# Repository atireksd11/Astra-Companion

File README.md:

# Astra Companion- sigma boy 124

This repo holds the carrier PCB, the voice stack on the laptop, and notes for building Astra. Week 1 was the KiCad board. This week we are finishing the **audio module** on the printed body: a side speaker box, a neck that can pan, and a clean path for wires through the pivot. The plastic lives in [Astra-Companion-Cad](https://github.com/atireksd11/Astra-Companion-Cad). Mic and amp are still on the PCB (INMP441 and MAX98357A).

The board is built around a **ESP32-S3-DEVKITC-1** so the expensive module can stay on headers. If the first spin has a dumb mistake, I can swap the DevKit without rebuying everything.

**Where things stand:** schematic and layout are in the repo but the board is **not fab ready yet**. Power nets and the DevKit 3V3 tie still needed cleanup in the last pass. Do not order Gerbers until every net is routed and DRC is clean.

## The PCB

MPU-6050 for balance, DRV8833 for two N20 channels, TP4056 + MT3608 + AP2112K for battery and rails, dual GC9A01 round displays on SPI, INMP441 and MAX98357A for audio, plus fuel gauge, RTC, ToF, and microSD on the schematic. For what is actually on the board right now, use [hardware/BOM2.md](hardware/BOM2.md) (the older planning list drifted).

Open the project in KiCad 10: [hardware/astracompanion/](hardware/astracompanion/). Parts list for grants: [hardware/bom.csv](hardware/bom.csv). Notes on cost tiers: [hardware/BOM_SUMMARY.md](hardware/BOM_SUMMARY.md). When routing is done, plot Gerbers into [hardware/src/](hardware/src/).

## This week: audio module and neck

The CAD shows how the speaker panel bolts to the side of the torso, how the driver sits behind the grille, and how the head stack sits on bearings so it can turn without chewing up PETG.

**Parts we ordered ($27.94 before tax and shipping)**

| Part | Qty | Unit | Total | Where |
|------|-----|------|-------|-------|
| [PGN 608-ZZ ball bearings, 10 pack](https://www.amazon.ca/gp/product/B07XLV1W2M/ref=ox_sc_act_title_2?smid=A3RMJZMAP3U4RK&psc=1) (8 by 22 by 7 mm) | 10 | $1.30 | $12.95 | Amazon.ca |
| [MG90S metal gear micro servo, 2 pack](https://www.amazon.ca/gp/product/B0BHYHKF2P/ref=ox_sc_act_title_1?smid=A1AEYBYG92X8UY&psc=1) | 2 | $7.50 | $14.99 | Amazon.ca |
| Tax and shipping | | | about $5 | Prime / domestic |

Unit price is per piece. The totals are the pack prices Amazon charges. The bearing pack gives you spares after you use two on the neck. The MG90S pack gives you one pan servo and one spare (or a future tilt). Full writeup and grant CSV: [hardware/BOM_AUDIO_MODULE.md](hardware/BOM_AUDIO_MODULE.md) and [hardware/bom-audio-module.csv](hardware/bom-audio-module.csv).

Exploded view of the head, speaker side panel, and neck stack:

Rear view with the vented speaker box on the body:

Inside the torso showing the speaker and board bay:

Side panel, gasket plates, and speaker mount detail:

Voice on the laptop (wake word, STT, TTS) is documented under [docs/VOICE_SETUP.md](docs/VOICE_SETUP.md) and [server/README.md](server/README.md). The robot firmware streams audio to that bridge when you are ready to test on hardware.

## Firmware

Arduino on ESP32 already runs FreeRTOS, so the firmware splits work that way on purpose.

On **core 0**, a balance loop reads the MPU6050, estimates tilt, and drives the DRV8833. That task does not touch SPI or WiFi so networking or display work cannot starve the PID loop.

On **core 1**, the UI task owns SPI and both GC9A01 eyes. It only redraws when the expression changes so it is not repainting 115k pixels for no reason.

Audio hardware is wired; streaming voice over the board is not in this firmware yet. Motors stay **off** until you type `motors on` in the serial monitor at 115200. Lift the wheels before you do that.

```bash
cd firmware
pio run -t upload
pio device monitor
```

Pin map: [docs/PINOUT.md](docs/PINOUT.md). More context: [docs/DEVELOPMENT.md](docs/DEVELOPMENT.md) and [firmware/README.md](firmware/README.md).

## What is in this repo

```
hardware/astracompanion/   KiCad schematic and PCB
hardware/bom.csv           grant import for the PCB parts
hardware/BOM2.md           BOM from the real schematic
firmware/                  PlatformIO project for the DevKit
docs/                      pinout, images, dev notes
```

## Power

USB C and the TP4056 charge an 18650. The MT3608 boosts for +5 V (motors, amp, LEDs). An AP2112K feeds +3.3 V logic. The displays use +3V3_DISP through a GPIO enable. Measure the rails with a multimeter before you seat the DevKit. Do not feed the boost output into the ESP32 3V3 pin.

The battery section can source enough current to make mistakes hot. Treat it like real hardware, not a breadboard toy.

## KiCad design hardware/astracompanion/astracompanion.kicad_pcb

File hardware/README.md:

# Hardware

Two Half Life tracks live here:

| Track | Week | Grant | BOM file | Status |
|-------|------|-------|----------|--------|
| **PCB + electronics** | 1 | Tier 2 (~$103 parts) | [`bom.csv`](bom.csv) | KiCad in [`astracompanion/`](astracompanion/); routing in progress |
| **CAD + mechanics** | 2 | Tier 1 (~$30) | [`bom-cad.csv`](bom-cad.csv) | Chassis modeled; see [`../docs/CAD.md`](../docs/CAD.md) |
| **Audio module + neck** | 2 | ~$28 parts | [`bom-audio-module.csv`](bom-audio-module.csv) | Bearings and MG90S pan; see [`BOM_AUDIO_MODULE.md`](BOM_AUDIO_MODULE.md) |

## Folders

```text
astracompanion/     KiCad 10 project (schematic + PCB)
bom.csv             Week 1 parts list for Half Life import
bom-cad.csv         Week 2 mechanical / print list
bom-audio-module.csv  Neck bearings and MG90S (this week)
BOM_AUDIO_MODULE.md Human notes + CAD images for the audio module
BOM2.md             Reference: parts on the schematic (not for HL import)
BOM_SUMMARY.md      Money math for PCB tier
BOM_CAD_SUMMARY.md  Money math for CAD tier
generated/          Netlist export from schematic
src/                Gerbers land here after a clean DRC plot
```

Root `BOM.md` is mirrored from Half Life and gets overwritten on sync. Edit **`bom.csv`** or **`bom-cad.csv`** in this folder for imports.

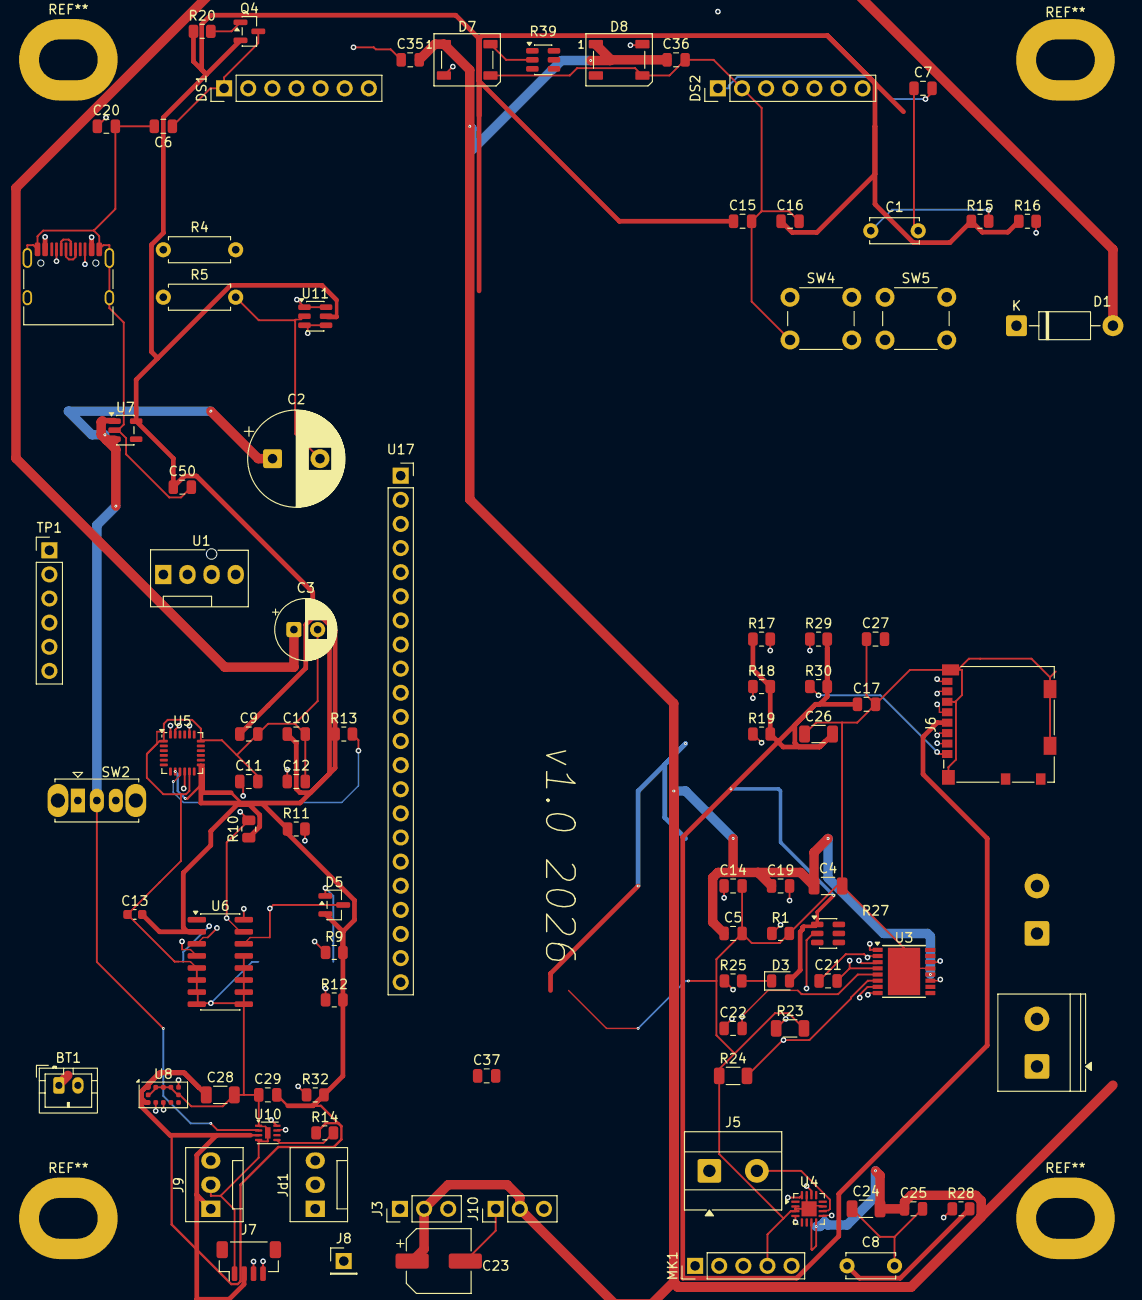
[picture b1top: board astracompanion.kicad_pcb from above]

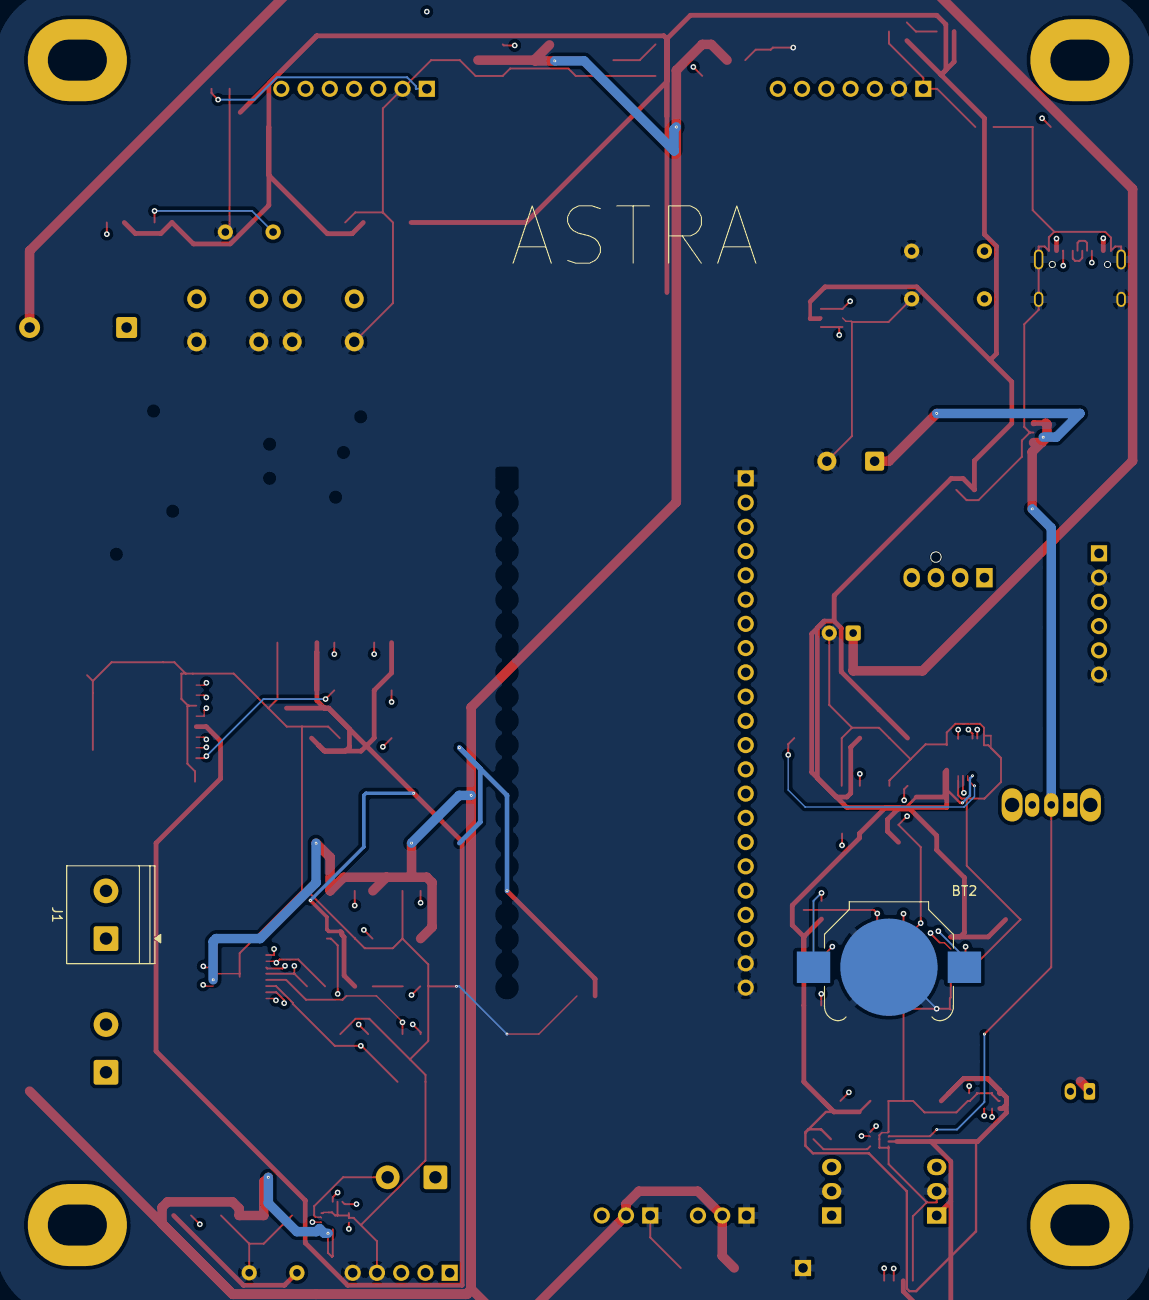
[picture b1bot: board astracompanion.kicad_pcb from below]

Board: 4 copper layers, 92 parts (2 on the bottom side), 59 nets.

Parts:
BT1: Battery_Cell; JST_PH_B2B-PH-K_1x02_P2.00mm_Vertical
BT2: Battery_Cell; BatteryHolder_Keystone_3000_1x12mm
C1: 1uF; C_Disc_D5.0mm_W2.5mm_P5.00mm
C2: 100uF; CP_Radial_D10.0mm_P5.00mm
C3: 1000uF; CP_Radial_D6.3mm_P2.50mm
C4, C24, C26, C28: 10uF; C_1206_3216Metric
C5, C6, C7, C9, C11, C16, C17, C21, C22, C25, C27, C29, C35, C36, C37: 0.1uF; C_0805_2012Metric
C8: 0.1uF; C_Disc_D5.0mm_W2.5mm_P5.00mm
C10, C19: 10nF; C_0805_2012Metric
C12: 2.2nF; C_0805_2012Metric
C13: 0.1uF; C_0603_1608Metric
C14, C50: 2.2uF; C_0805_2012Metric
C15: 10uF; C_0805_2012Metric
C20: 22uF; C_0805_2012Metric
C23: 100uF; CP_Elec_6.3x5.4
D1: 1N5819; D_DO-41_SOD81_P10.16mm_Horizontal
D3: LED; LED_0805_2012Metric
D5: BAT54C; SOT-23
D7: WS2812B-5050; LED_WS2812B_PLCC4_5.0x5.0mm_P3.2mm
D8: WS2812B; LED_WS2812B_PLCC4_5.0x5.0mm_P3.2mm
DS1, DS2: 1.28" 240x240 LCD; PinHeader_1x07_P2.54mm_Vertical
J1, J2: Screw_Terminal_01x02; TerminalBlock_Phoenix_PT-1,5-2-5.0-H_1x02_P5.00mm_Horizontal
J3, J10: Conn_01x03_Pin; PinHeader_1x03_P2.54mm_Vertical
J4: USB_C_Receptacle_USB2.0; USB_C_Receptacle_HRO_TYPE-C-31-M-12
J5: Conn_01x02_Socket; TerminalBlock_MetzConnect_Type055_RT01502HDWU_1x02_P5.00mm_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
J6: Micro_SD_Card; microSD_HC_Molex_104031-0811
J7: Conn_01x04_Socket; JST_SH_BM04B-SRSS-TB_1x04-1MP_P1.00mm_Vertical
J8: testpoint; PinHeader_1x01_P2.54mm_Vertical
J9: Encoder_L; FanPinHeader_1x03_P2.54mm_Vertical
Jd1: Encoder_R; FanPinHeader_1x03_P2.54mm_Vertical
MK1: INMP441ACEZ-R7; PinHeader_1x05_P2.54mm_Vertical
Q4: AO3401A; SOT-23
R1, R9, R12, R13, R14, R15, R16, R17, R18, R19, R20, R29, R30, R32: 10k; R_0805_2012Metric
R4, R5: 5.1K; R_Axial_DIN0207_L6.3mm_D2.5mm_P7.62mm_Horizontal
R10, R11: 2.2k; R_0805_2012Metric
R23, R24: 0.2; R_1206_3216Metric
R25: 1k; R_0805_2012Metric
R27: 10k; SOT-23-6
R28: 100k; R_0805_2012Metric
R39: 330; SOT-23-6
SW2: SW_SPST; SW_Slide_SPDT_Straight_CK_OS102011MS2Q
SW4: Reset / EN button; SW_PUSH_6mm
SW5: Boot / IO0 button; SW_PUSH_6mm
TP1: PinHeader_1x06_P2.54mm_Vertical
U1: MT3608_BOOSTER_MODULE; FanPinHeader_1x04_P2.54mm_Vertical
U3: DRV8833PWP; HTSSOP-16-1EP_4.4x5mm_P0.65mm_EP3.4x5mm
U4: MAX98357A; TQFN-16-1EP_3x3mm_P0.5mm_EP1.6x1.6mm
U5: MPU-6050; InvenSense_QFN-24_4x4mm_P0.5mm
U6: DS3231M; SOIC-16_3.9x9.9mm_P1.27mm
U7: AP2112K-3.3; SOT-23-5
U8: VL53L0CXV0DH1; ST_VL53L1x
U10: MAX17048G+T10; DFN-8-1EP_2x2mm_P0.5mm_EP0.6x1.2mm
U11: USBLC6-2SC6; SOT-23-6
U17: Conn_01x22_Pin; PinSocket_1x22_P2.54mm_Vertical

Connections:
+3V3: C8.1, C9.1, C10.1, C13.2, C15.1, C16.1, C17.1, C26.2, C27.2, C28.1, C29.2, C37.1, C50.1, D3.2 (A), D5.2, J6.4 (VDD), J7.2, J9.1, Jd1.1, Q4.2 (S), R9.2, R10.1, R11.1, R12.2, R13.1, R14.1, R15.1, R16.1, R17.1, R18.2, R19.2, R20.1, R27.1, R28.2, R29.2, R30.2, R32.2, U5.8 (VLOGIC), U5.13 (VDD), U6.2 (VCC), U7.5 (VOUT), U8.1 (AVDDVCSEL), U8.11 (AVDD), U10.3 (VDD), U11.5 (VBUS)
+3V3_DISP: C6.1, C7.2, C20.1, DS1.1 (VCC), DS2.1 (VCC), Q4.3 (D)
+5V: C3.1, C4.1, C5.1, C19.1, C23.1, C24.2, C25.1, C35.2, C36.1, D1.2 (A), D7.1 (VDD), D8.1 (VDD), J3.2, J10.2, U3.12 (VM), U4.7 (VDD), U4.8 (VDD)
/B-: BT1.2 (-), TP1.4 (B-)
B+: BT1.1 (+), TP1.3 (B+)
DISP_PWR_EN: Q4.1 (G), R20.2
ESP_RST: C1.1, DS1.7 (RST), DS2.7 (RST), R15.2, SW4.1
FG_INT: R14.2, U10.5 (~ALRT)
GND: BT2.2 (-), C1.2, C2.2, C3.2, C4.2, C5.2, C6.2, C7.1, C8.2, C9.2, C10.2, C11.2, C12.2, C13.1, C14.2, C15.2, C16.2, C17.2, C20.2, C23.2, C24.1, C25.2, C26.1, C27.1, C28.2, C29.1, C35.1, C36.2, C37.2, C50.2, D7.3 (VSS), D8.3 (VSS), DS1.2 (GND), DS2.2 (GND), J3.1, J4.A1 (GND), J4.A12 (GND), J4.B1 (GND), J4.B12 (GND), J4.SH (SHIELD), J6.6 (VSS), J6.SH (SHIELD), J7.1, J8.1 (Pin_1_1), J9.2, J10.1, Jd1.2, MK1.4 (L/R), MK1.5 (GND), R1.2, R4.2, R5.2, R23.2, R24.1, SW4.2, SW5.2, TP1.2 (-), TP1.6 (OUT-), U3.13 (GND), U3.17 (GND), U4.2 (GAIN_SLOT), U4.3 (GND), U4.11 (GND), U4.15 (GND), U4.17 (PAD), U5.1 (CLKIN), U5.11 (FSYNC), U5.18 (GND), U6.5 (GND), U6.6 (GND), U6.7 (GND), U6.8 (GND), U6.9 (GND), U6.10 (GND), U6.11 (GND), U6.12 (GND), U6.13 (GND), U7.2 (GND), U8.2 (AVSSVCSEL), U8.3 (GND), U8.4 (GND), U8.6 (GND), U8.12 (GND), U10.1 (CTG), U10.4 (GND), U10.9 (EP), U11.2 (GND), U17.1, U17.21, U17.22
I2C_SCL: J7.4, R11.2, U5.23 (SCL), U6.16 (SCL), U8.10 (SCL), U10.7 (SCL), U11.3 (I/O2), U11.4 (I/O2)
I2C_SDA: J7.3, R10.2, U5.24 (SDA), U6.15 (SDA), U8.9 (SDA), U10.8 (SDA), U11.1 (I/O1), U11.6 (I/O1)
I2S_BCLK: MK1.1 (SCK), U4.16 (BCLK), U17.15
I2S_DOUT: U4.1 (DIN), U17.2
I2S_LRCK: MK1.3 (WS), U4.14 (LRCLK), U17.16
MOTOR_L_DIR: U3.9 (BIN1), U17.8
MOTOR_L_PWM: U3.10 (BIN2), U17.9
MOTOR_R_DIR: U3.16 (AIN1), U17.6
MOTOR_R_PWM: U3.15 (AIN2), U17.7
M_FAULT: R25.1, R27.2, U3.8 (~FAULT)
M_SLP: R1.1, U3.1 (~SLEEP)
unnamed: BT2.1 (+), D5.1
unnamed: D3.1 (K), R25.2
unnamed: D7.4 (DIN), R39.2
unnamed: D7.2 (DOUT), D8.4 (DIN)
unnamed: C21.1, J1.1, U3.2 (AOUT1)
unnamed: C21.2, J1.2, U3.4 (AOUT2)
unnamed: C22.1, J2.1, U3.7 (BOUT1)
unnamed: C22.2, J2.2, U3.5 (BOUT2)
unnamed: J4.A5 (CC1), R4.1
unnamed: J4.B5 (CC2), R5.1
unnamed: J5.1, U4.9 (OUTP)
unnamed: J5.2, U4.10 (OUTN)
unnamed: J6.8 (DAT1), R29.1
unnamed: J6.1 (DAT2), R30.1
unnamed: R23.1, U3.3 (AISEN)
unnamed: R24.2, U3.6 (BISEN)
unnamed: C19.2, U3.11 (VCP)
unnamed: C14.1, U3.14 (VINT)
unnamed: R28.1, U4.4 (~SD_MODE)
unnamed: R13.2, U5.9 (AD0)
unnamed: C12.1, U5.20 (CPOUT)
unnamed: C11.1, U5.10 (REGOUT)
unnamed: D5.3, U6.14 (VBAT)
unnamed: R9.1, U6.4 (~RST)
unnamed: R16.2, SW5.1, U17.14
OUT+: SW2.1 (A), TP1.5 (OUT+)
RGB_DATA: R39.1, U17.10
RTC_INT: R12.1, U6.3 (~INT/SQW)
SD_CS: J6.2 (DAT3/CD), R19.1, U17.18
SERVO_PWM: J3.3, J10.3
SPI_CLK: DS1.3 (SCL), DS2.3 (SCL), J6.5 (CLK)
SPI_MISO: J6.7 (DAT0), R18.1, U17.17
SPI_MOSI: DS1.4 (SDA), DS2.4 (SDA), J6.3 (CMD), R17.2
TFT_DC: DS1.5 (DC), DS2.5 (DC)
TOF_XSHUT: R32.1, U8.5 (XSHUT)
USB_D+: J4.A6 (D+), J4.B6 (D+), U17.19
USB_D-: J4.A7 (D-), J4.B7 (D-), U17.20
VBAT: C2.1, SW2.2 (B), U7.1 (VIN), U7.3 (EN), U10.2 (CELL)
VBUS: J4.A4 (VBUS), J4.A9 (VBUS), J4.B4 (VBUS), J4.B9 (VBUS), TP1.1 (5V+)

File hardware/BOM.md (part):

# Astra Companion — bill of materials

<!-- Generated by Half Life from project cmuvgfgnh00a901q9t8ie3rrb. Edits here are overwritten on the next sync. -->
<!-- Generated: 1970-01-01T00:00:00.000Z -->

> [!NOTE]
> This parts list is mirrored from [Half Life](https://halflife.hackclub.com). Editing it here will not change the platform's copy, and the next sync overwrites this file.

| Week | Tier | Parts funding |
| --- | --- | --- |
| Week 1 | Tier 2 | $65.00 |

The importer that already read this repo uses `hardware/bom.csv` with columns Part, Purpose, Qty, Unit Price (USD), Total Price (USD), Vendor, Link, Notes. Root `BOM.md` has no part columns of its own. The table below is the same list. Qty is the quantity that has to be purchased. PCB manufacturing, shipping, and tax are not included.


| Part | Purpose | Qty | Unit Price (USD) | Total Price (USD) | Vendor | Link | Notes |
| --- | --- | --- | --- | --- | --- | --- | --- |
| ESP32-S3-DEVKITC-1-N8R8 | Main controller. Plugs into U2. | 1 | 15.00 | 15.00 | Mouser | https://www.mouser.com/ProductDetail/Espressif-Systems/ESP32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 | Existing vendor and link kept. Page not reopened on 2026-10-12. Buy 1. |
| DRV8833PWPR | Dual H-bridge. U3. | 1 | 2.10 | 2.10 | LCSC | https://www.lcsc.com/product-detail/C50506.html | Existing vendor and link kept. Page not reopened on 2026-10-12. Buy 1. |
| GC9A01 1.28in 240x240 round LCD module | Round eyes. DS1 and DS2. | 2 | 8.90 | 17.80 | Makerfabs | https://www.makerfabs.com/gc9a01-1-28-inch-round-lcd-module.html | Existing vendor and link kept. Page not reopened on 2026-10-12. Buy 2. |
| MPU-6050 | Balance gyro. U5 bare QFN. | 1 | 20.23 | 20.23 | LCSC | https://www.lcsc.com/product-detail/C24112.html | Existing vendor and link kept. Page not reopened on 2026-10-12. Buy 1. A cheaper module is a later cost cut. The design is unchanged. |
| DS3231M+TRL | Real-time clock. U6. 16-pin wide SOIC. | 1 | 14.29 | 14.29 | DigiKey | https://www.digikey.com/en/products/detail/analog-devices-in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 | Checked 2026-10-12. Cut-tape price. Package on the page is 16-SOIC, 0.295 inch (7.50 mm) wide. This is not the 8-pin MZ part. Digi-Reel would add a $7 fee, which is not included. |
| VL53L0CXV0DH/1 | Distance sensor. U8. | 1 | 5.18 | 5.18 | Mouser | https://www.mouser.com/ProductDetail/STMicroelectronics/VL53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 | Existing vendor and link kept. Page not reopened on 2026-10-12. Buy 1. The board footprint is still the VL53L1x pattern. |
| MAX98357AETE+T | I2S speaker amplifier. U4. | 1 | 1.33 | 1.33 | LCSC | https://www.lcsc.com/product-detail/C910544.html | Existing vendor and link kept. Page not reopened on 2026-10-12. Buy 1. |
| INMP441 I2S microphone module, 6-pin | Microphone. MK1. | 1 |  |  |  |  | Needs a page that states 6 pins and a USD price. The Elecrow page opened on 2026-10-12 is $5.00 but does not say the pin count. |
| MAX17048G+T10 | Fuel gauge. U10. | 1 | 2.17 | 2.17 | LCSC | https://www.lcsc.com/product-detail/C2682616.html | Existing vendor and link kept. Page not reopened on 2026-10-12. Buy 1. |
| MT3608 boost module | Motor-rail boost. U1. | 1 | 0.95 | 0.95 | ProtoSupplies | https://protosupplies.com/product/mt3608-mini-adjustable-dc-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 | Existing vendor and link kept. Page not reopened on 2026-10-12. Buy 1. |
| AP2112K-3.3TRG1 | 3.3V regulator. U7. | 5 | 0.08 | 0.40 | LCSC | https://www.lcsc.com/product-detail/C51118.html | Existing vendor and link kept. Page not reopened on 2026-10-12. Minimum buy is 5. One is used. |
| AO3401A | Display power switch. Q4. | 10 | 0.06 | 0.60 | LCSC | https://www.lcsc.com/product-detail/C15127.html | Existing vendor and link kept. Page not reopened on 2026-10-12. Minimum buy is 10. One is used. |
| USBLC6-2SC6 | USB ESD diode. U11. | 5 | 0.18 | 0.90 | LCSC | https://www.lcsc.com/product-detail/C7519.html | Existing vendor and link kept. Page not reopened on 2026-10-12. Minimum buy is 5. One is used. |
| USBLC6-4SC6 | ESD diode. U13. | 5 | 0.17 | 0.85 | LCSC | https://www.lcsc.com/product-detail/C111212.html | Existing vendor and link kept. Page not reopened on 2026-10-12. Minimum buy is 5. One is used. |
| TYPE-C-31-M-12 | USB-C receptacle. J4. | 5 | 0.19 | 0.95 | LCSC | https://www.lcsc.com/product-detail/C165948.html | Existing vendor and link kept. Page not reopened on 2026-10-12. Minimum buy is 5. One is used. |
| PTS645 tactile switch | User buttons. SW1 SW3 SW6. | 5 | 0.21 | 1.05 | LCSC | https://www.lcsc.com/product-detail/C221880.html | Existing vendor and link kept. Page not reopened on 2026-10-12. Minimum buy is 5. Three are used. |
| WS2812B | Status LEDs. D7 and D8. | 5 | 0.10 | 0.50 | LCSC | https://www.lcsc.com/product-detail/C114586.html | Existing vendor and link kept. Page not reopened on 2026-10-12. Minimum buy is 5. Two are used. |
| 0.1uF 0805 capacitor | Decoupling. | 20 | 0.02 | 0.40 | LCSC | https://www.lcsc.com/product-detail/C1711.html | Existing vendor and link kept. Page not reopened on 2026-10-12. Minimum buy is 20. Eighteen 0805 parts are on the board. |
| TP4056 USB-C charger module with DW01 | Charger. TP1. | 1 |  |  |  |  | Needs a USD page. The module must show IN+ IN- B+ B- OUT+ OUT- and a DW01 chip. No page opened on 2026-10-12 stated all of that in USD. |
| Slide switch | Power switch. SW2. | 1 |  |  |  |  | Schematic footprint name is SW_Slide_SPDT_Straight_CK_OS102011MS2Q. No USD page opened on 2026-10-12. |
| Molex 1040310811 microSD slot | Card socket. J6. | 1 | 2.21 | 2.21 | DigiKey | https://www.digikey.com/en/products/detail/molex/1040310811/2370379 | Checked 2026-10-12. Cut-tape price for one. Description: microSD card connector, surface mount, right angle. Digi-Reel would add a $7 fee, which is not included. |
| CR2032 coin cell holder | Coin cell holder. BT2. | 1 |  |  |  |  | Footprint name is BatteryHolder_Keystone_3000. No price page opened on 2026-10-12. |
| CR2032 coin cell | Cell for BT2. | 1 |  |  |  |  | No price page opened on 2026-10-12. |
| BAT54C | Diode. D5. | 1 |  |  |  |  | No price page opened on 2026-10-12. |
| 1N5819 | Schottky diode. D1. | 1 |  |  |  |  | No price page opened on 2026-10-12. |
| Phoenix screw terminal 1x2 | J1 and J2. | 2 |  |  |  |  | No price page opened on 2026-10-12. |
| Metz screw terminal 1x2 | J5. | 1 |  |  |  |  | No price page opened on 2026-10-12. |
| Pin header 1x7 | Display connectors. DS1 and DS2. | 2 |  |  |  |  | No price page opened on 2026-10-12. |
| Pin header 1x6 | Header for the TP4056 module. TP1. | 1 |  |  |  |  | No price page opened on 2026-10-12. |
| Pin header 1x4 | Header for the boost module. U1. | 1 |  |  |  |  | No price page opened on 2026-10-12. |
| JST SH 4-pin 1.0 mm connector plus cable | I2C connector. J7. | 1 |  |  |  |  | Needs one listing that includes the connector and the cable. No price page opened on 2026-10-12. |
| Pin header 1x3 | Servo headers. J3 and J10. | 2 |  |  |  |  | No price page opened on 2026-10-12. |
| Fan pin header 1x3 | Encoder connectors. J9 and Jd1. | 2 |  |  |  |  | No price page opened on 2026-10-12. |
| Pin header 1x1 | Test point. J8. | 1 |  |  |  |  | No price page opened on 2026-10-12. |
| Female header 1x22 | Sockets for the DevKit. | 2 |  |  |  |  | No price page opened on 2026-10-12. The symbol has 22 pins per side. The placed footprint is 2x19. |
| JST PH 2-pin plus 18650 holder with leads | Battery plug and holder. BT1. | 1 |  |  |  |  | No single page opened on 2026-10-12 sells this pair. The Keystone 1042 row is deleted because that footprint is not on the board. |
| 10k 0805 resistor | Pull-ups. R1 R9 R12 R13 R14 R15 R16 R17 R18 R19 R20 R27 R29 R30 R32 R36 R37 R38. | 100 | 0.0034 | 0.34 | LCSC | https://www.lcsc.com/product-detail/C881248.html | Checked 2026-10-12. EVER OHMS CR0805F10K0P05Z, 10k 1% 0805. Need 18. Minimum purchase is 100 at $0.0034, total $0.34. |
| 5.1k axial resistor | R4 and R5. | 2 |  |  |  |  | No price page opened on 2026-10-12. |
| 2.2k 0805 resistor | R10 and R11. | 2 |  |  |  |  | No price page opened on 2026-10-12. |
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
